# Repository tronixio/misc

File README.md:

# Misc.

## Schematics.

- [Capacitors Board.](https://github.com/tronixio/misc/blob/main/Kicad/capacitors/extras/schematic.pdf)
- [Resistors Board.](https://github.com/tronixio/misc/blob/main/Kicad/resistors/extras/schematic.pdf)

## CAPACITORS Board Top.

## CAPACITORS Board Bottom.

## RESISTORS Board Top.

## RESISTORS Board Bottom.

## Notes.

- DRAFT : Prototype OK, last check schematic, PCB & code can be modify.
- TODO : Work in progress, prototype was not good, hardware, PCB and code can be rework.

---

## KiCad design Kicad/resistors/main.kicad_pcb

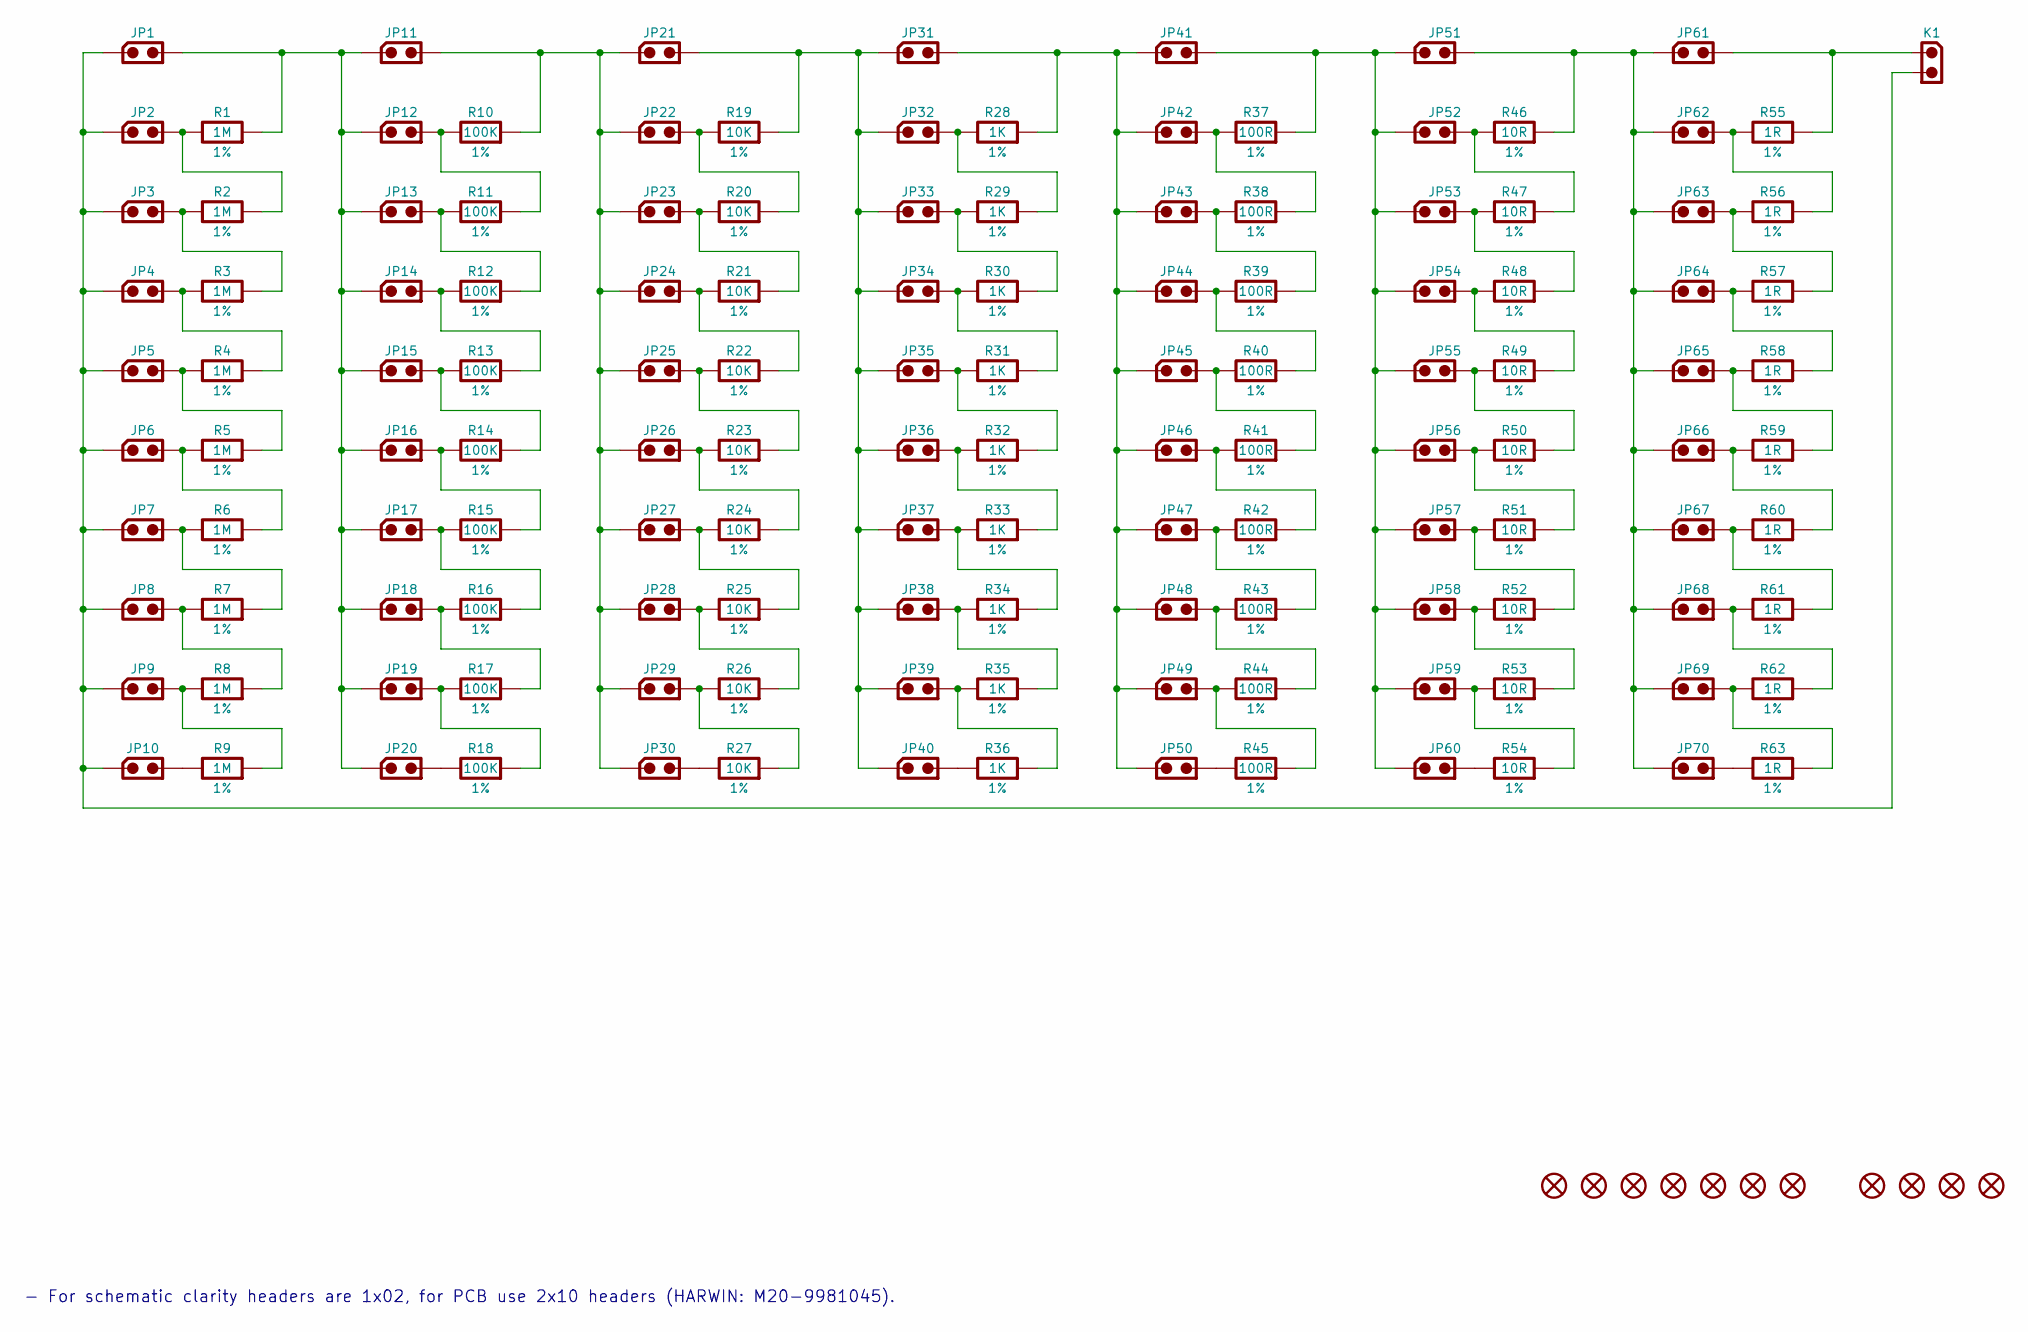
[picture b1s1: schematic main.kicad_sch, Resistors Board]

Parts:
H1, H2, H3, H4: KEYSTONE-9056; Mouser 534-9056
JP1, JP2, JP3, JP4, JP5, JP6, JP7, JP8, JP9, JP10, JP11, JP12, JP13, JP14, JP15, JP16, JP17, JP18, JP19, JP20, JP21, JP22, JP23, JP24, JP25, JP26, JP27, JP28, JP29, JP30, JP31, JP32, JP33, JP34, JP35, JP36, JP37, JP38, JP39, JP40, JP41, JP42, JP43, JP44, JP45, JP46, JP47, JP48, JP49, JP50, JP51, JP52, JP53, JP54, JP55, JP56, JP57, JP58, JP59, JP60, JP61, JP62, JP63, JP64, JP65, JP66, JP67, JP68, JP69, JP70: HARWIN-M20-999024x; Mouser 855-M20-999024
JP71, JP72, JP73, JP74, JP75, JP76, JP77: HARWIN-JUMPER-0254-14MM-BLACK; HARWIN-M20-7680-7683; Mouser 855-M7682
K1: R; HARWIN-M20-999024x; Mouser 855-M20-999024
R1, R2, R3, R4, R5, R6, R7, R8, R9: 1M; RESISTOR-SMD-1206; Tolerance 1%; Mouser 603-RT1206FRE071ML
R10, R11, R12, R13, R14, R15, R16, R17, R18: 100K; RESISTOR-SMD-1206; Tolerance 1%; Mouser 603-RT1206FRE07100KL
R19, R20, R21, R22, R23, R24, R25, R26, R27: 10K; RESISTOR-SMD-1206; Tolerance 1%; Mouser 603-RT1206FRE1310KL
R28, R29, R30, R31, R32, R33, R34, R35, R36: 1K; RESISTOR-SMD-1206; Tolerance 1%; Mouser 603-RT1206FRE071KL
R37, R38, R39, R40, R41, R42, R43, R44, R45: 100R; RESISTOR-SMD-1206; Tolerance 1%; Mouser 603-RT1206FRE07100RL
R46, R47, R48, R49, R50, R51, R52, R53, R54: 10R; RESISTOR-SMD-1206; Tolerance 1%; Mouser 603-RT1206FRE0710RL
R55, R56, R57, R58, R59, R60, R61, R62, R63: 1R; RESISTOR-SMD-1206; Tolerance 1%; Mouser 603-RT1206FRE071RL

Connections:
unnamed: JP1.1, JP2.1, JP3.1, JP4.1, JP5.1, JP6.1, JP7.1, JP8.1, JP9.1, JP10.1, K1.2
unnamed: JP1.2, JP11.1, JP12.1, JP13.1, JP14.1, JP15.1, JP16.1, JP17.1, JP18.1, JP19.1, JP20.1, R1.2
unnamed: JP2.2, R1.1, R2.2
unnamed: JP3.2, R2.1, R3.2
unnamed: JP4.2, R3.1, R4.2
unnamed: JP5.2, R4.1, R5.2
unnamed: JP6.2, R5.1, R6.2
unnamed: JP7.2, R6.1, R7.2
unnamed: JP8.2, R7.1, R8.2
unnamed: JP9.2, R8.1, R9.2
unnamed: JP10.2, R9.1
unnamed: JP11.2, JP21.1, JP22.1, JP23.1, JP24.1, JP25.1, JP26.1, JP27.1, JP28.1, JP29.1, JP30.1, R10.2
unnamed: JP12.2, R10.1, R11.2
unnamed: JP13.2, R11.1, R12.2
unnamed: JP14.2, R12.1, R13.2
unnamed: JP15.2, R13.1, R14.2
unnamed: JP16.2, R14.1, R15.2
unnamed: JP17.2, R15.1, R16.2
unnamed: JP18.2, R16.1, R17.2
unnamed: JP19.2, R17.1, R18.2
unnamed: JP20.2, R18.1
unnamed: JP21.2, JP31.1, JP32.1, JP33.1, JP34.1, JP35.1, JP36.1, JP37.1, JP38.1, JP39.1, JP40.1, R19.2
unnamed: JP22.2, R19.1, R20.2
unnamed: JP23.2, R20.1, R21.2
unnamed: JP24.2, R21.1, R22.2
unnamed: JP25.2, R22.1, R23.2
unnamed: JP26.2, R23.1, R24.2
unnamed: JP27.2, R24.1, R25.2
unnamed: JP28.2, R25.1, R26.2
unnamed: JP29.2, R26.1, R27.2
unnamed: JP30.2, R27.1
unnamed: JP31.2, JP41.1, JP42.1, JP43.1, JP44.1, JP45.1, JP46.1, JP47.1, JP48.1, JP49.1, JP50.1, R28.2
unnamed: JP32.2, R28.1, R29.2
unnamed: JP33.2, R29.1, R30.2
unnamed: JP34.2, R30.1, R31.2
unnamed: JP35.2, R31.1, R32.2
unnamed: JP36.2, R32.1, R33.2
unnamed: JP37.2, R33.1, R34.2
unnamed: JP38.2, R34.1, R35.2
unnamed: JP39.2, R35.1, R36.2
unnamed: JP40.2, R36.1
unnamed: JP41.2, JP51.1, JP52.1, JP53.1, JP54.1, JP55.1, JP56.1, JP57.1, JP58.1, JP59.1, JP60.1, R37.2
unnamed: JP42.2, R37.1, R38.2
unnamed: JP43.2, R38.1, R39.2
unnamed: JP44.2, R39.1, R40.2
unnamed: JP45.2, R40.1, R41.2
unnamed: JP46.2, R41.1, R42.2
unnamed: JP47.2, R42.1, R43.2
unnamed: JP48.2, R43.1, R44.2
unnamed: JP49.2, R44.1, R45.2
unnamed: JP50.2, R45.1
unnamed: JP51.2, JP61.1, JP62.1, JP63.1, JP64.1, JP65.1, JP66.1, JP67.1, JP68.1, JP69.1, JP70.1, R46.2
unnamed: JP52.2, R46.1, R47.2
unnamed: JP53.2, R47.1, R48.2
unnamed: JP54.2, R48.1, R49.2
unnamed: JP55.2, R49.1, R50.2
unnamed: JP56.2, R50.1, R51.2
unnamed: JP57.2, R51.1, R52.2
unnamed: JP58.2, R52.1, R53.2
unnamed: JP59.2, R53.1, R54.2
unnamed: JP60.2, R54.1
unnamed: JP61.2, K1.1, R55.2
unnamed: JP62.2, R55.1, R56.2
unnamed: JP63.2, R56.1, R57.2
unnamed: JP64.2, R57.1, R58.2
unnamed: JP65.2, R58.1, R59.2
unnamed: JP66.2, R59.1, R60.2
unnamed: JP67.2, R60.1, R61.2
unnamed: JP68.2, R61.1, R62.2
unnamed: JP69.2, R62.1, R63.2
unnamed: JP70.2, R63.1

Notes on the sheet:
- For schematic clarity headers are 1x02, for PCB use 2x10 headers (HARWIN: M20-9981045).

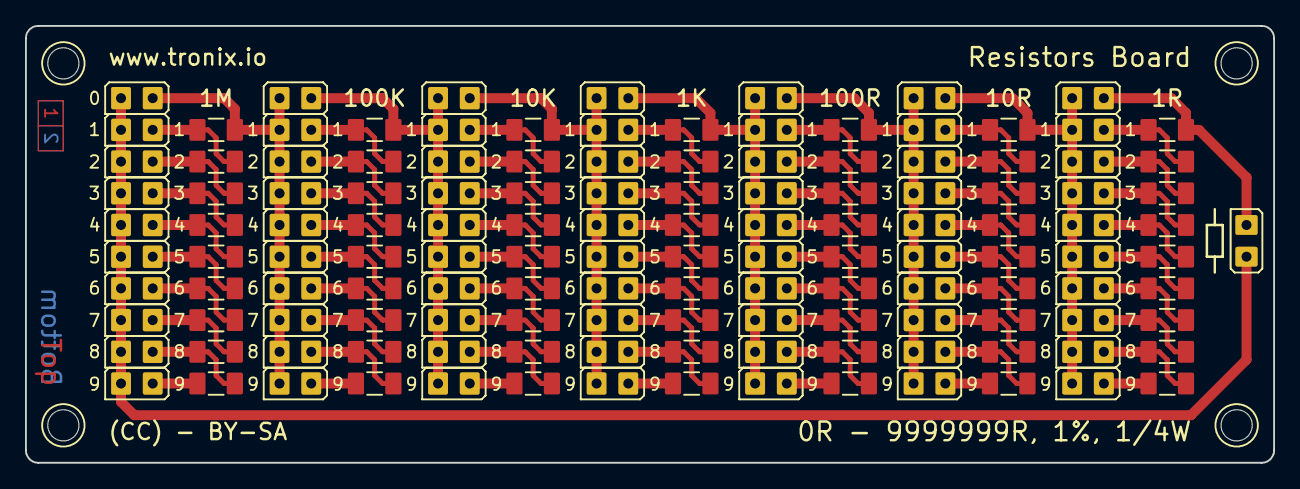
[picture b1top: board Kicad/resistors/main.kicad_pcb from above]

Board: 2 copper layers, 100.0 x 35.0 mm, 146 parts (1 on the bottom side), 71 nets.

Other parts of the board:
GB: LOGO; OSHW-5MM

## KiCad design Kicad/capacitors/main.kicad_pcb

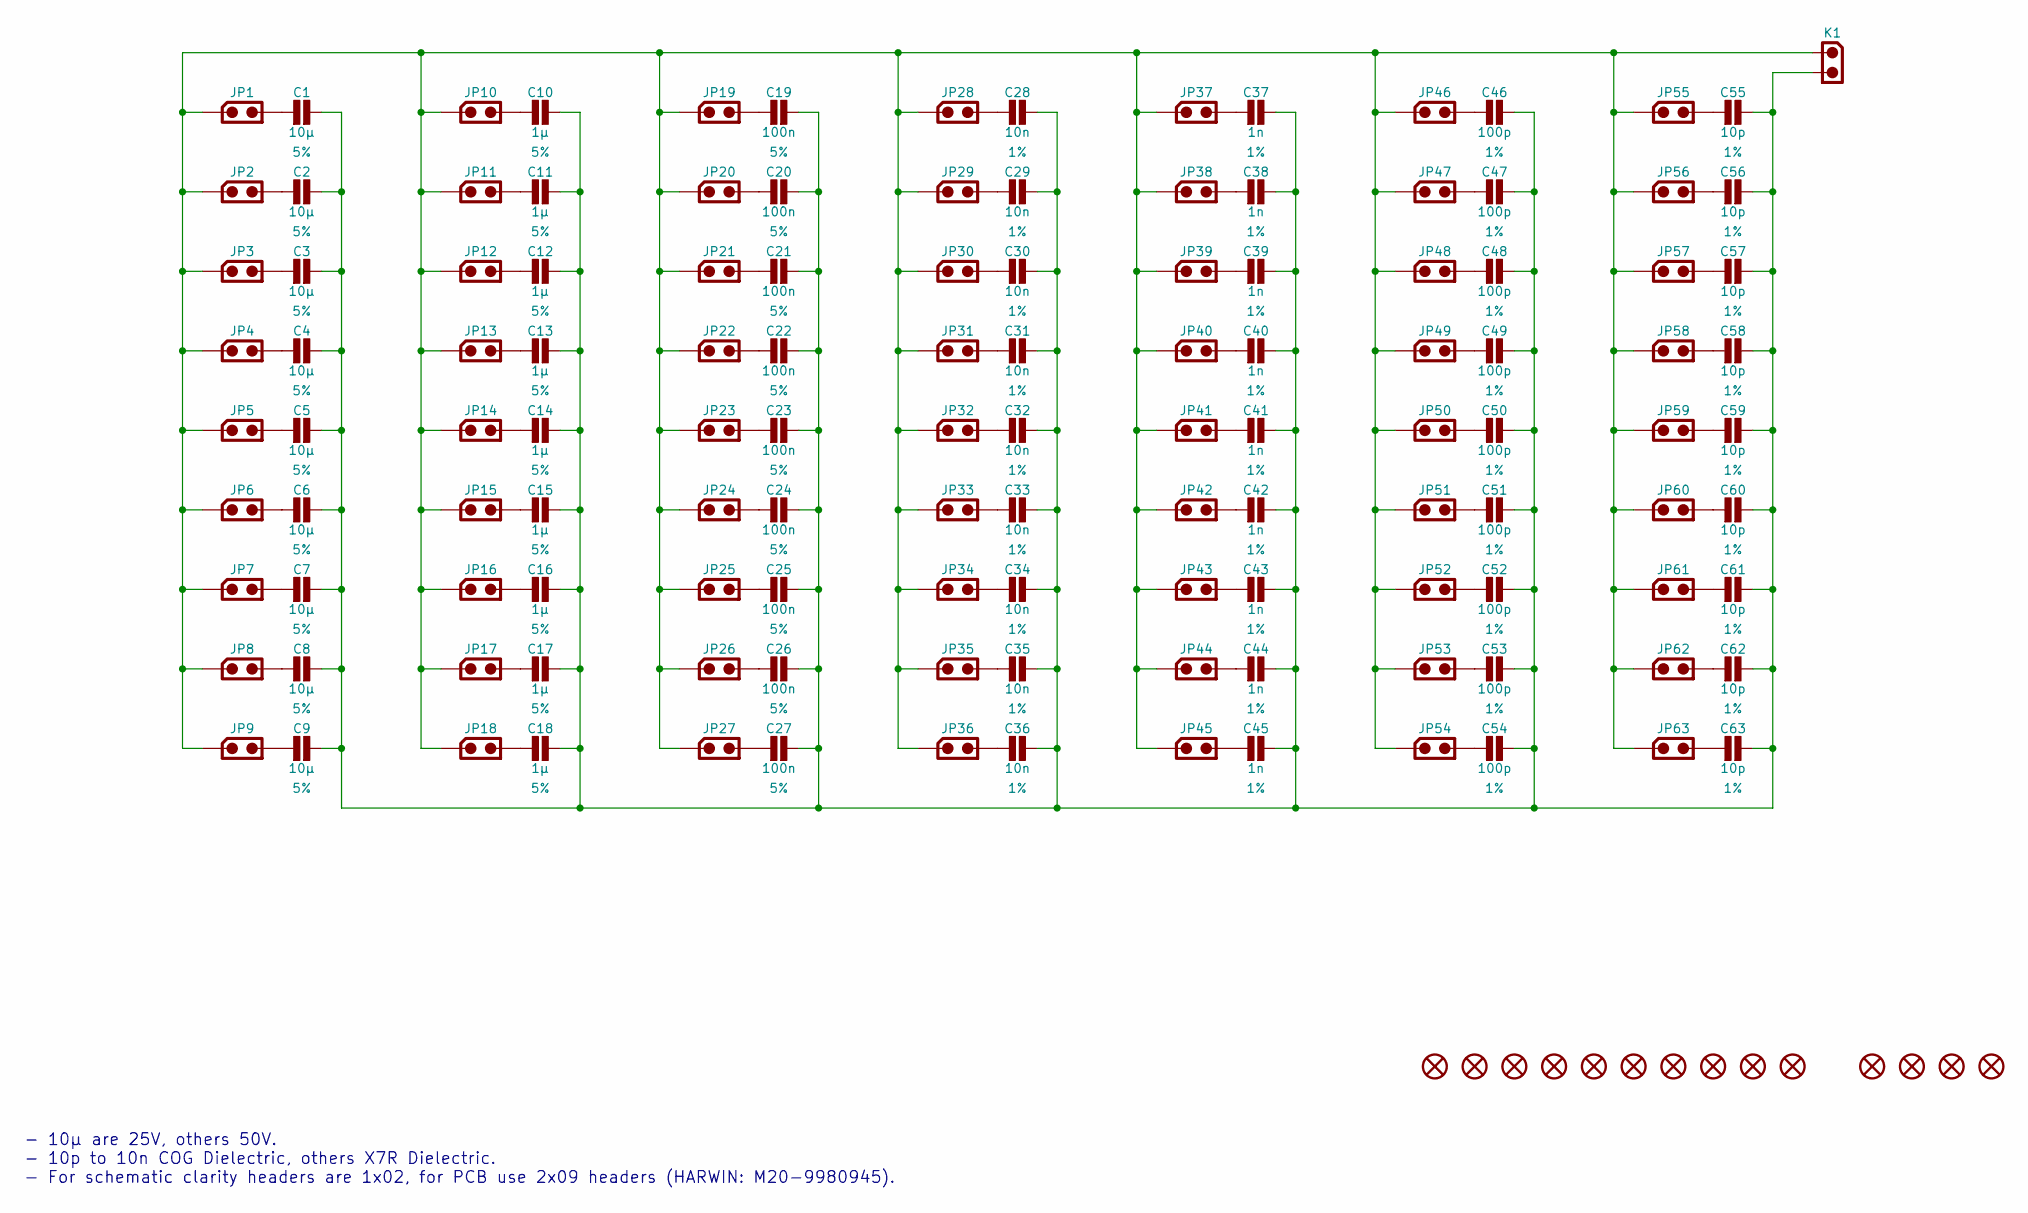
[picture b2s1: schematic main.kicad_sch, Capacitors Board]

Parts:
C1, C2, C3, C4, C5, C6, C7, C8, C9: 10µ; CAPACITOR-SMD-1206; Voltage 25V; Tolerance 5%; Mouser 80-C1206C106J3R
C10, C11, C12, C13, C14, C15, C16, C17, C18: 1µ; CAPACITOR-SMD-1206; Voltage 50V; Tolerance 5%; Mouser 80-C1206C105J5
C19, C20, C21, C22, C23, C24, C25, C26, C27: 100n; CAPACITOR-SMD-1206; Voltage 50V; Tolerance 5%; Mouser 80-C1206C104J5R
C28, C29, C30, C31, C32, C33, C34, C35, C36: 10n; CAPACITOR-SMD-1206; Voltage 50V; Tolerance 1%; Mouser 80-C1206C103F5GECTU
C37, C38, C39, C40, C41, C42, C43, C44, C45: 1n; CAPACITOR-SMD-1206; Voltage 50V; Tolerance 1%; Mouser 81-GRM3195C1H223FA1
C46, C47, C48, C49, C50, C51, C52, C53, C54: 100p; CAPACITOR-SMD-1206; Voltage 50V; Tolerance 1%; Mouser 80-C1206C101F5G
C55, C56, C57, C58, C59, C60, C61, C62, C63: 10p; CAPACITOR-SMD-1206; Voltage 100V; Tolerance 1%; Mouser 581-12061A100FAT2A
H1, H2, H3, H4: KEYSTONE-9056; Mouser 534-9056
JP1, JP2, JP3, JP4, JP5, JP6, JP7, JP8, JP9, JP10, JP11, JP12, JP13, JP14, JP15, JP16, JP17, JP18, JP19, JP20, JP21, JP22, JP23, JP24, JP25, JP26, JP27, JP28, JP29, JP30, JP31, JP32, JP33, JP34, JP35, JP36, JP37, JP38, JP39, JP40, JP41, JP42, JP43, JP44, JP45, JP46, JP47, JP48, JP49, JP50, JP51, JP52, JP53, JP54, JP55, JP56, JP57, JP58, JP59, JP60, JP61, JP62, JP63: HARWIN-M20-999024x; Mouser 855-M20-999024
JP64, JP65, JP66, JP67, JP68, JP69, JP70, JP71, JP72, JP73: HARWIN-JUMPER-0254-14MM-BLACK; HARWIN-M20-7680-7683; Mouser 855-M7682
K1: Capacitor; HARWIN-M20-999024x; Mouser 855-M20-999024

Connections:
unnamed: C1.1, JP1.2
unnamed: C1.2, C2.2, C3.2, C4.2, C5.2, C6.2, C7.2, C8.2, C9.2, C10.2, C11.2, C12.2, C13.2, C14.2, C15.2, C16.2, C17.2, C18.2, C19.2, C20.2, C21.2, C22.2, C23.2, C24.2, C25.2, C26.2, C27.2, C28.2, C29.2, C30.2, C31.2, C32.2, C33.2, C34.2, C35.2, C36.2, C37.2, C38.2, C39.2, C40.2, C41.2, C42.2, C43.2, C44.2, C45.2, C46.2, C47.2, C48.2, C49.2, C50.2, C51.2, C52.2, C53.2, C54.2, C55.2, C56.2, C57.2, C58.2, C59.2, C60.2, C61.2, C62.2, C63.2, K1.2
unnamed: C2.1, JP2.2
unnamed: C3.1, JP3.2
unnamed: C4.1, JP4.2
unnamed: C5.1, JP5.2
unnamed: C6.1, JP6.2
unnamed: C7.1, JP7.2
unnamed: C8.1, JP8.2
unnamed: C9.1, JP9.2
unnamed: C10.1, JP10.2
unnamed: C11.1, JP11.2
unnamed: C12.1, JP12.2
unnamed: C13.1, JP13.2
unnamed: C14.1, JP14.2
unnamed: C15.1, JP15.2
unnamed: C16.1, JP16.2
unnamed: C17.1, JP17.2
unnamed: C18.1, JP18.2
unnamed: C19.1, JP19.2
unnamed: C20.1, JP20.2
unnamed: C21.1, JP21.2
unnamed: C22.1, JP22.2
unnamed: C23.1, JP23.2
unnamed: C24.1, JP24.2
unnamed: C25.1, JP25.2
unnamed: C26.1, JP26.2
unnamed: C27.1, JP27.2
unnamed: C28.1, JP28.2
unnamed: C29.1, JP29.2
unnamed: C30.1, JP30.2
unnamed: C31.1, JP31.2
unnamed: C32.1, JP32.2
unnamed: C33.1, JP33.2
unnamed: C34.1, JP34.2
unnamed: C35.1, JP35.2
unnamed: C36.1, JP36.2
unnamed: C37.1, JP37.2
unnamed: C38.1, JP38.2
unnamed: C39.1, JP39.2
unnamed: C40.1, JP40.2
unnamed: C41.1, JP41.2
unnamed: C42.1, JP42.2
unnamed: C43.1, JP43.2
unnamed: C44.1, JP44.2
unnamed: C45.1, JP45.2
unnamed: C46.1, JP46.2
unnamed: C47.1, JP47.2
unnamed: C48.1, JP48.2
unnamed: C49.1, JP49.2
unnamed: C50.1, JP50.2
unnamed: C51.1, JP51.2
unnamed: C52.1, JP52.2
unnamed: C53.1, JP53.2
unnamed: C54.1, JP54.2
unnamed: C55.1, JP55.2
unnamed: C56.1, JP56.2
unnamed: C57.1, JP57.2
unnamed: C58.1, JP58.2
unnamed: C59.1, JP59.2
unnamed: C60.1, JP60.2
unnamed: C61.1, JP61.2
unnamed: C62.1, JP62.2
unnamed: C63.1, JP63.2
unnamed: JP1.1, JP2.1, JP3.1, JP4.1, JP5.1, JP6.1, JP7.1, JP8.1, JP9.1, JP10.1, JP11.1, JP12.1, JP13.1, JP14.1, JP15.1, JP16.1, JP17.1, JP18.1, JP19.1, JP20.1, JP21.1, JP22.1, JP23.1, JP24.1, JP25.1, JP26.1, JP27.1, JP28.1, JP29.1, JP30.1, JP31.1, JP32.1, JP33.1, JP34.1, JP35.1, JP36.1, JP37.1, JP38.1, JP39.1, JP40.1, JP41.1, JP42.1, JP43.1, JP44.1, JP45.1, JP46.1, JP47.1, JP48.1, JP49.1, JP50.1, JP51.1, JP52.1, JP53.1, JP54.1, JP55.1, JP56.1, JP57.1, JP58.1, JP59.1, JP60.1, JP61.1, JP62.1, JP63.1, K1.1

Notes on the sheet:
- 10µ are 25V, others 50V. - 10p to 10n COG Dielectric, others X7R Dielectric. - For schematic clarity headers are 1x02, for PCB use 2x09 headers (HARWIN: M20-9980945).

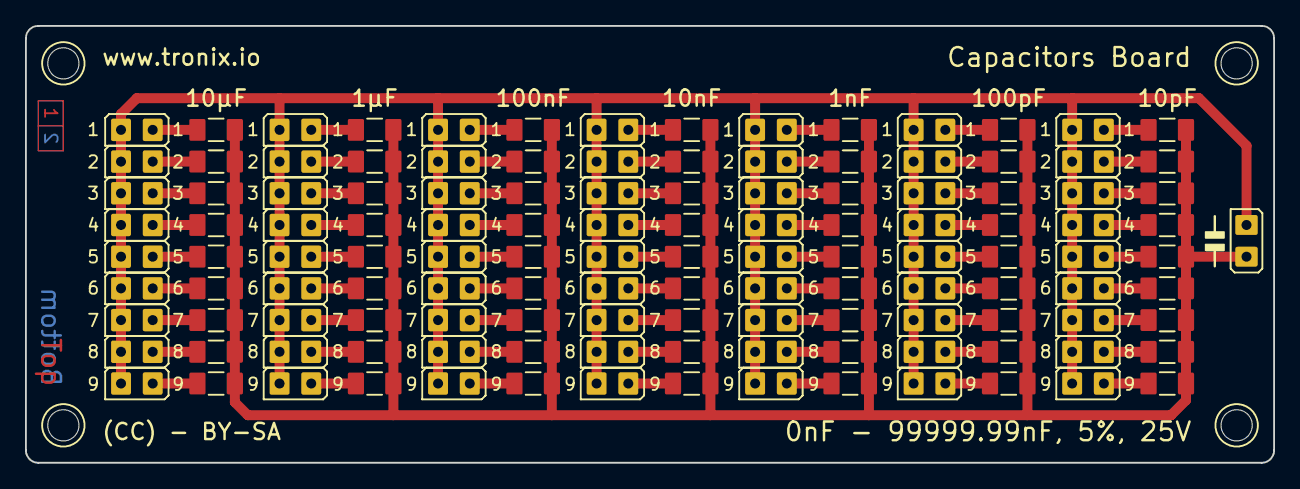
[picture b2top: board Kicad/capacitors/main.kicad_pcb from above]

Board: 2 copper layers, 100.0 x 35.0 mm, 142 parts (1 on the bottom side), 65 nets.

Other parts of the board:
GB: LOGO; OSHW-5MM

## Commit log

2022-03-27 Capacitor
2022-03-27 Resistor
2022-03-27 Update Resistor Board
2022-03-27 Update Capacitor
2022-03-27 Update Resistor
2023-10-10 Up capacitors
2023-10-13 Update capacitors
2023-10-15 Up resistors
2023-10-17 Up resistor
